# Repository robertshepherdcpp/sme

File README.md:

SME (as in same)

## motivation
- i thought it would be cool to have a thing with ur friends/family where u can know ur thinking of each other at the same time no matter the location in a physical thing. not just test.

## what is it? / how does it work
- you will have one and another person will have one
- when u press the button on each of ur own projects, a sound will play!
- using adafruit api

##  assembly instructions
- purchase all the things detailed in the BOM.csv file in this repository
- then print out the case and the pcb
- get an sd card, and save the audio file in this repository (or one of your choice!) to it.
- then insert it into the holder in the pcb.
- then insert the pcb into the case
- put the lid on
- then screw in using the 3 screws going through.
- then you can plug the esp32 (at the bottom of the case) into a computer
- and then you need to configure your api keys etc in the firmware.
- then flash the firmware! (easiest way to do this is using the arduino ide)
- then u can connect with another project!
- have fun!

## pcb
schematic:

pcb wiring:

3d model:

cad:

BOM:

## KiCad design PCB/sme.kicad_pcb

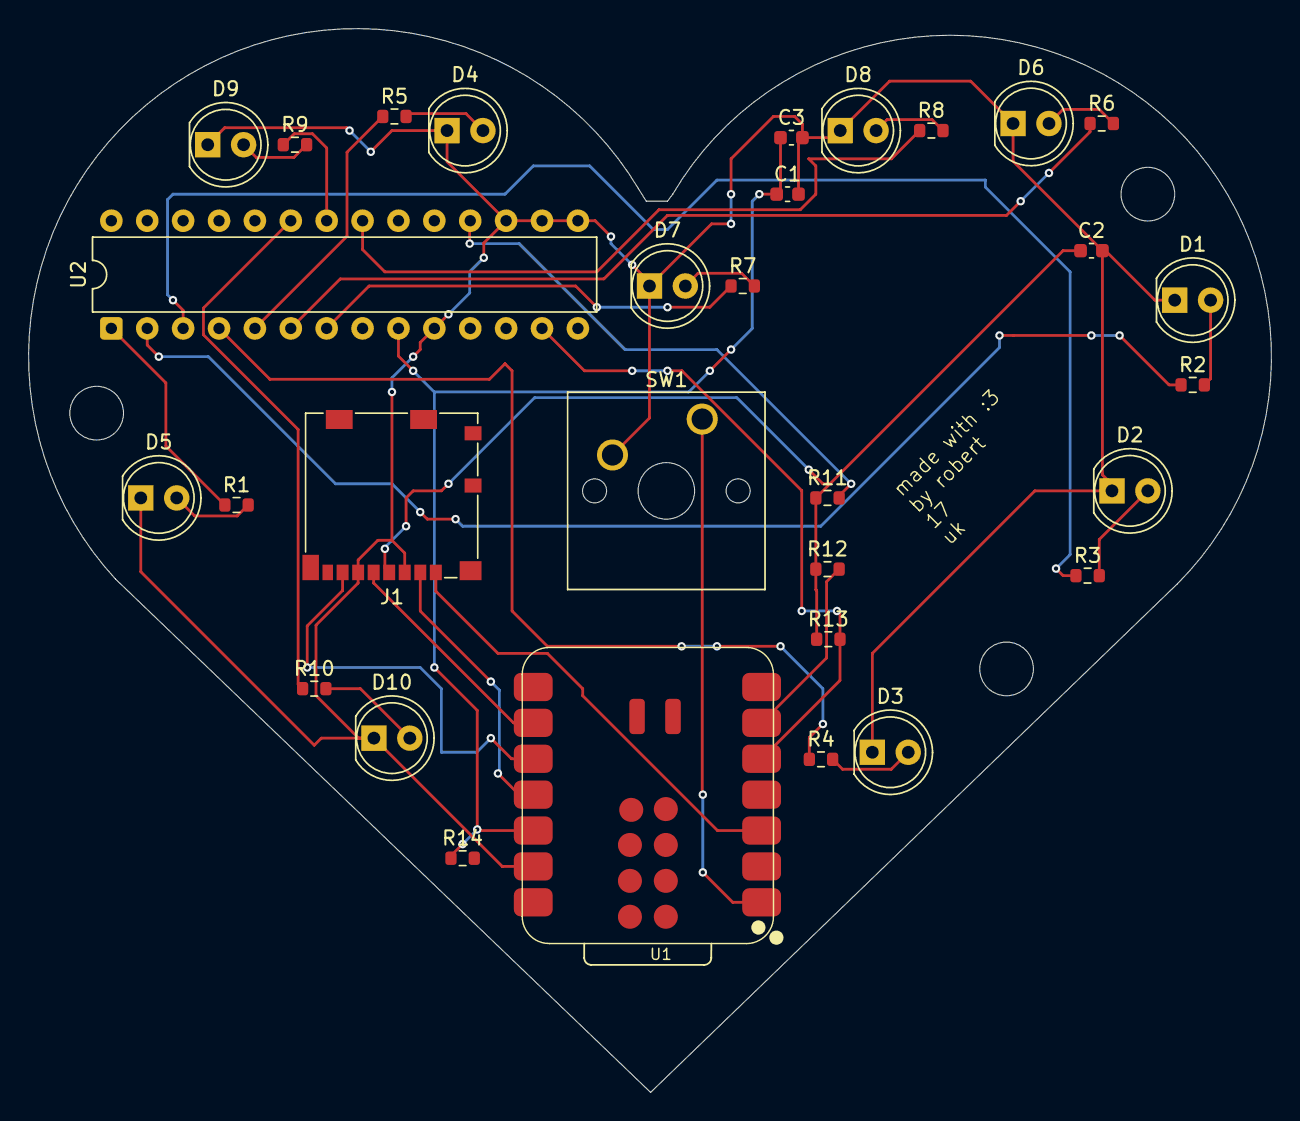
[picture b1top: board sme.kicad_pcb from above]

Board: 2 copper layers, 88.0 x 75.3 mm, 31 parts (0 on the bottom side), 31 nets.

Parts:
C1: 0.1uF; C_0603_1608Metric
C2: 10uF; C_0603_1608Metric
C3: 10u; C_0603_1608Metric
D1, D2, D3, D4, D5, D6, D7, D8, D9, D10: LED; LED_D5.0mm
J1: SD_Card_Receptacle; microSD_HC_Molex_104031-0811
R1, R2, R3, R4, R5, R6, R7, R8, R9, R10: 100; R_0603_1608Metric
R11, R14: 10k; R_0603_1608Metric
R12, R13: R; R_0603_1608Metric
SW1: SW_Push; SW_Cherry_MX_1.00u_PCB
U1: XIAO-ESP32-C6-SMD
U2: MCP23017_SP; DIP-28_W7.62mm

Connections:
23017_SDA: R13.2, U1.5 (GPIO22_D4_SDA), U2.13 (SDA)
23017_SDK: R12.2, U1.6 (GPIO23_D5_SCL)
+3.3V: C1.1, C3.1, R14.1, U1.12 (3V3), U2.9 (VDD)
+3V3: C2.1, J1.4 (VDD), R11.1, R12.1, R13.1
GND: C1.2, C2.2, C3.2, D1.1 (K), D2.1 (K), D3.1 (K), D4.1 (K), D5.1 (K), D6.1 (K), D7.1 (K), D8.1 (K), D9.1 (K), D10.1 (K), J1.3 (VSS), J1.6 (VSS), SW1.2, U1.13 (GND), U2.10 (VSS), U2.15 (A0), U2.16 (A1), U2.17 (A2)
MISO: J1.7 (DAT0), U1.10 (GPIO20_D9_MISO)
MOSI: J1.2 (CMD), U1.11 (GPIO18_D10_MOSI)
unnamed: D1.2 (A), R2.2
unnamed: D2.2 (A), R3.2
unnamed: D3.2 (A), R4.2
unnamed: D4.2 (A), R5.2
unnamed: D5.2 (A), R1.2
unnamed: D6.2 (A), R6.2
unnamed: D7.2 (A), R7.2
unnamed: D8.2 (A), R8.2
unnamed: D9.2 (A), R9.2
unnamed: D10.2 (A), R10.2
unnamed: R8.1, U2.21 (GPA0)
unnamed: R9.1, U2.22 (GPA1)
unnamed: R10.1, U2.23 (GPA2)
unnamed: R1.1, U2.1 (GPB0)
unnamed: R2.1, U2.2 (GPB1)
unnamed: R3.1, U2.3 (GPB2)
unnamed: R4.1, U2.4 (GPB3)
unnamed: R5.1, U2.5 (GPB4)
unnamed: R6.1, U2.6 (GPB5)
unnamed: R7.1, U2.7 (GPB6)
unnamed: R11.2, U2.18 (~RESET)
SD_CS: J1.1 (CD/DAT3), U1.3 (GPIO2_A2_D2)
SD_SCK: J1.5 (CLK), U1.9 (GPIO19_D8_SCK)
button: SW1.1, U1.1 (GPIO0_A0_D0)

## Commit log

2026-06-21 add the pcb files.
2026-06-21 Clarify SME acronym in README
2026-06-21 add 3d model
2026-06-21 Rename sme.step to CAD/sme.step
2026-06-21 add the fusion file.
2026-06-21 add the zine.
2026-06-21 Rename Untitled (27).pdf to zine/Untitled (27).pdf
2026-06-21 Enhance README with project description and usage
    Added explanation of project functionality and usage.
